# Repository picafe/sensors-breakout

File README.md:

# Sensors Breakout

Small 4-layer KiCad PCB that packs a RTC and several I²C and SPI sensors into a compact board (around 3x1.5 cm) for cheap assembly, lots of config options, and testing sensors.

---

## What it is

A breakout board of the **PCF8563 RTC**, **Sensirion SHT41** temperature/humidity sensor on an I²C bus. There is a **STMicro LSM6DSV** IMU connected over SPI with a 7-pin JST SH connector, and **QST QMC6309** magnetometer connected over I²C to the LSM6DSV's sensorhub with level shifting.

1.8 V power + logic for the RTC, temp sensor, and IMU, while keeping the magnetometer at 3.3 V via a LDO and BSS138 level shifter, so the design stays compatible with economic JLC PCBA (since QMC6309 is the only precise magnetometer offered with economic PCBA).

---

## Motivation

The board started as a quick PCF8563 test board which would go on a few of my other projects, and now is a general purpose board for testing sensors, with QWIIC-style connectors (JST SH).

---

## Features

| Area | Detail |
|------|--------|
| **RTC** | PCF8563 + crystal |
| **Temp/Humidity** | SHT41 (can be populated from a cheap breakout or omitted) |
| **Motion** | LSM6DSV 6-axis IMU |
| **Magnetometer** | QMC6309 |

- **Power:** 1.8 V rail for core I²C peripherals; 3.3 V LDO, VBAT input, and level shifting for magnetometer
- **Interface:** QWIIC-compatible connector; optional status LED with 3‑pad solder jumper (auto / manual pin / off)

---

## Current design

3D view:

---

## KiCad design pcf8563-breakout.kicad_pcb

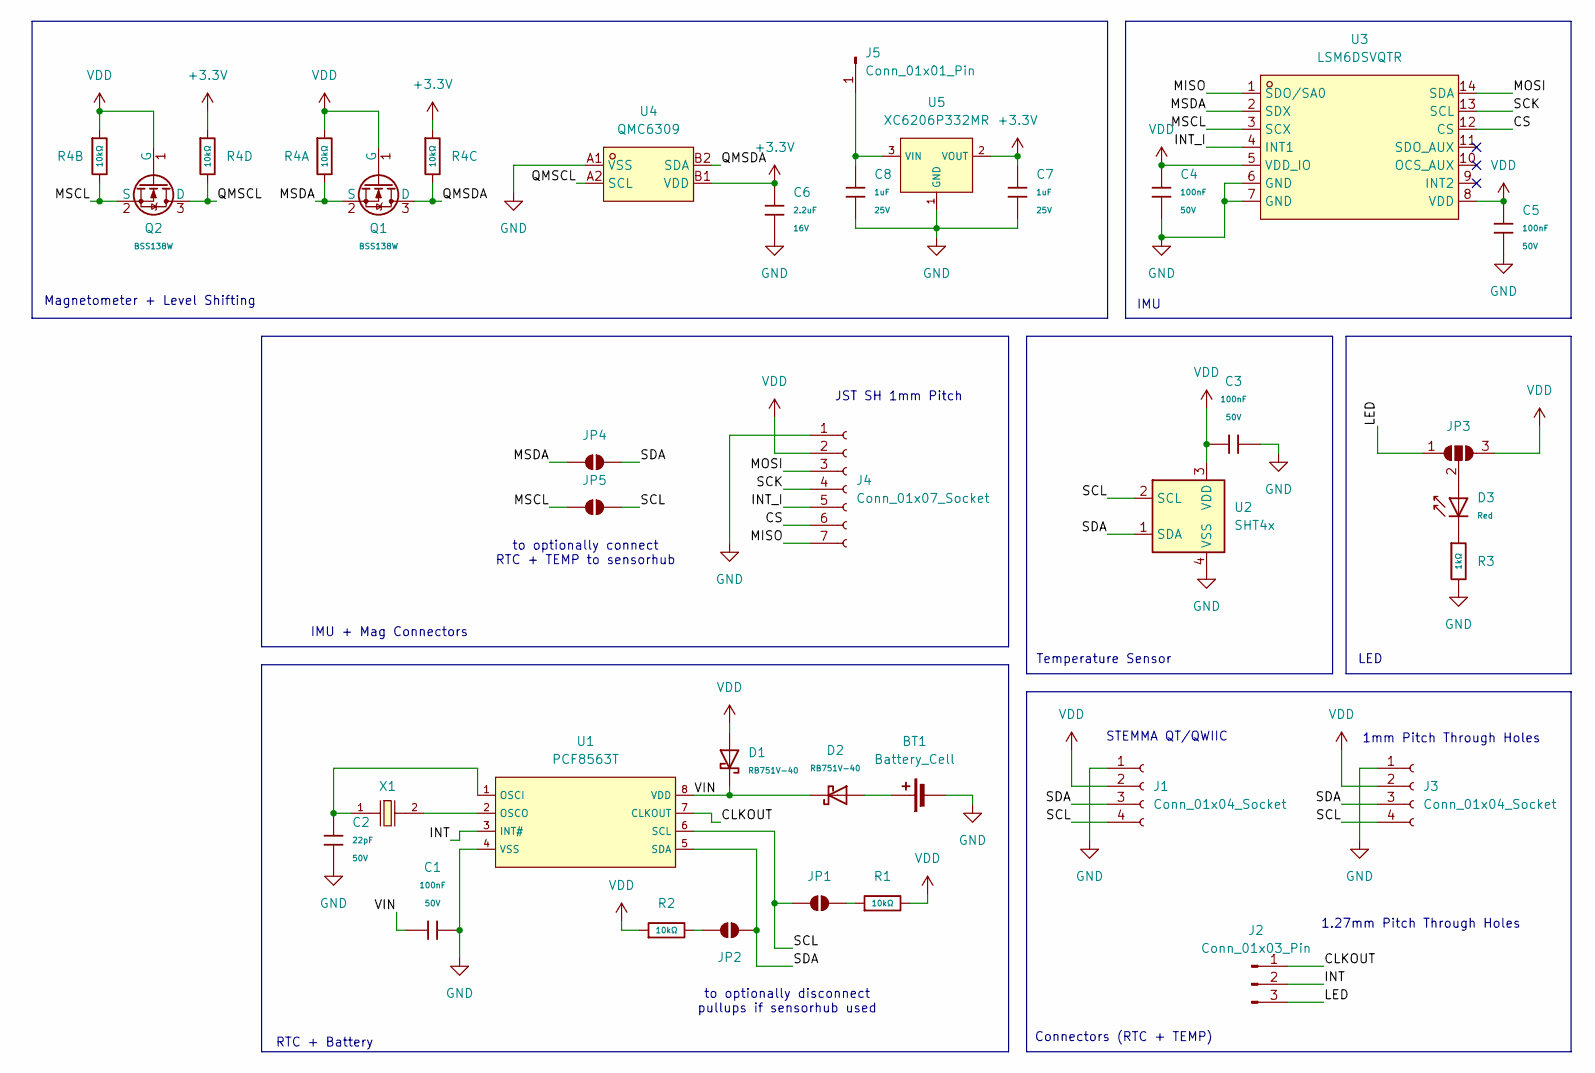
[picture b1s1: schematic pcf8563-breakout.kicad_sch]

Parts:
BT1: Battery_Cell; BAT-SMD_BS-CR2032-8
C1, C3, C4, C5: 100nF; C_0402; Voltage Rated 50V; Tolerance ±10%; Part CL05B104KB54PNC; LCSC C307331
C2: 22pF; C_0402; Voltage Rated 50V; Tolerance ±5%; Part 0402CG220J500NT; LCSC C1555
C6: 2.2uF; C_0603; Voltage Rated 16V; Tolerance ±10%; Part CL10A225KO8NNNC; LCSC C23630
C7, C8: 1uF; C_0402; Voltage Rated 25V; Tolerance ±10%; Part CL05A105KA5NQNC; LCSC C52923
D1, D2: RB751V-40; D_SOD-323; Forward Voltage (Vf@If) 370mV@1mA; Reverse Voltage (Vr) 40V; Part RB751V-40; LCSC C7502691
D3: Red; D_0603; Part KT-0603R; LCSC C2286
J1: Conn_01x04_Socket; JST_SH_SM04B-SRSS-TB_1x04-1MP_P1.00mm_Horizontal
J2: Conn_01x03_Pin; PinSocket_1x03_P1.27mm_Vertical
J3: Conn_01x04_Socket; PinSocket_1x04_P1.00mm_Vertical
J4: Conn_01x07_Socket; JST_SH_SM07B-SRSS-TB_1x07-1MP_P1.00mm_Horizontal
J5: Conn_01x01_Pin; PinHeader_1x01_P1.27mm_Vertical
JP1, JP2, JP4, JP5: SolderJumper_2_Open; SolderJumper-2-Sparkfun
JP3: SolderJumper_3_Open; SolderJumper-3-Sparkfun
Q1, Q2: BSS138W; Q_SOT-323; Part BSS138W; LCSC C28646265
R1, R2: 10kΩ; R_0402; Overload Voltage (Max) 50V; Tolerance ±1%; Part 0402WGF1002TCE; LCSC C25744
R3: 1kΩ; R_0603; Overload Voltage (Max) 75V; Tolerance ±1%; Part 0603WAF1001T5E; LCSC C21190
R4: 10kΩ; R_0402x4; Tolerance ±5%; Part 4D02WGJ0103TCE; LCSC C25725
U1: PCF8563T; SOIC-8_3.9x4.9mm_P1.27mm; Operating Voltage 1V~5.5V; Part PCF8563T/5,518; LCSC C7440
U2: SHT4x; Sensirion_DFN-4_1.5x1.5mm_P0.8mm_SHT4x_NoCentralPad
U3: LSM6DSVQTR; LGA-14_L3.0-W2.5-P0.50-TL; MPN LSM6DSVTR; LCSC Part C5267399
U4: QMC6309; X1-WLB0808-4_L0.8-W0.8-P0.40-TL; MPN QMC6309; LCSC Part C5439871
U5: XC6206P332MR; SOT-23-3_L2.9-W1.6-P1.90-LS2.8-BR; Output Voltage 3.3V; Dropout Voltage 680mV@(100mA); Part XC6206P332MR-G; LCSC C5446
X1: Q13FC1350000400; FC-135R_L3.2-W1.5; Frequency Tolerance ±20ppm; Part Q13FC13500004; LCSC C32346

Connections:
+3.3V: C6.1, C7.1, R4.3, R4.4, U4.B1 (VDD), U5.2 (VOUT)
/CLKOUT: J2.1, U1.7 (CLKOUT)
/CS: J4.6, U3.12 (CS)
/INT: J2.2, U1.3 (INT#)
/INT_I: J4.5, U3.4 (INT1)
/LED: J2.3, JP3.1 (A)
/MISO: J4.7, U3.1 (SDO/SA0)
/MOSI: J4.3, U3.14 (SDA)
/MSCL: JP5.1 (A), Q2.2 (S), R4.7, U3.3 (SCX)
/MSDA: JP4.1 (A), Q1.2 (S), R4.8, U3.2 (SDX)
/QMSCL: Q2.3 (D), R4.5, U4.A2 (SCL)
/QMSDA: Q1.3 (D), R4.6, U4.B2 (SDA)
/SCK: J4.4, U3.13 (SCL)
/SCL: J1.4, J3.4, JP1.1 (A), JP5.2 (B), U1.6 (SCL), U2.2 (SCL)
/SDA: J1.3, J3.3, JP2.1 (A), JP4.2 (B), U1.5 (SDA), U2.1 (SDA)
/VIN: C1.1, D1.1, D2.1, U1.8 (VDD)
GND: BT1.2 (-), C1.2, C2.2, C3.2, C4.1, C5.1, C6.2, C7.2, C8.2, J1.1, J3.1, J4.1, R3.2, U1.4 (VSS), U2.4 (VSS), U3.6 (GND), U3.7 (GND), U4.A1 (VSS), U5.1 (GND)
unnamed: BT1.1 (+), D2.2
unnamed: D3.1, R3.1
unnamed: C8.1, J5.1, U5.3 (VIN)
unnamed: JP1.2 (B), R1.1
unnamed: JP2.2 (B), R2.2
unnamed: D3.2, JP3.2 (C)
unnamed: C2.1, U1.1 (OSCI), X1.1
unnamed: U1.2 (OSCO), X1.2
VDD: C3.1, C4.2, C5.2, D1.2, J1.2, J3.2, J4.2, JP3.3 (B), Q1.1 (G), Q2.1 (G), R1.2, R2.1, R4.1, R4.2, U2.3 (VDD), U3.5 (VDD_IO), U3.8 (VDD)

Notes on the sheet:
Connectors (RTC + TEMP)
Temperature Sensor
to optionally connect RTC + TEMP to sensorhub
IMU
to optionally disconnect pullups if sensorhub used
JST SH 1mm Pitch
1mm Pitch Through Holes
IMU + Mag Connectors
RTC + Battery
1.27mm Pitch Through Holes
STEMMA QT/QWIIC
Magnetometer + Level Shifting
LED

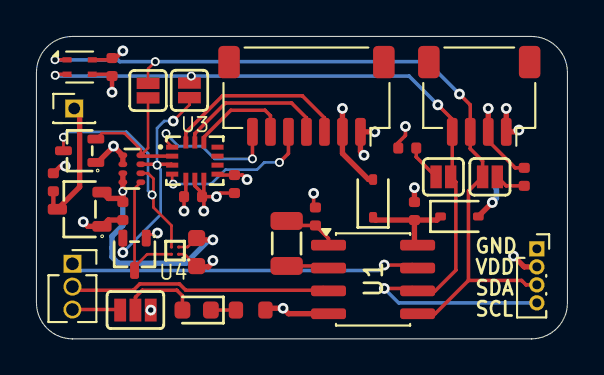
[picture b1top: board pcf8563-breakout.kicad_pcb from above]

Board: 4 copper layers, 29.5 x 16.8 mm, 34 parts (1 on the bottom side), 26 nets.

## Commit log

2026-04-28 init
2026-04-29 feat: updates and journal
2026-04-29 Rename journal.md to JOURNAL.md
2026-04-29 fix: journal formatting
2026-04-30 feat: readme
2026-04-30 fix: readme
2026-05-03 feat: pcb fix
